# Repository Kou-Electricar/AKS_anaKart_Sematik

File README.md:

# AKS_anaKart_Sematik
araç kontrol kartı ana kartı

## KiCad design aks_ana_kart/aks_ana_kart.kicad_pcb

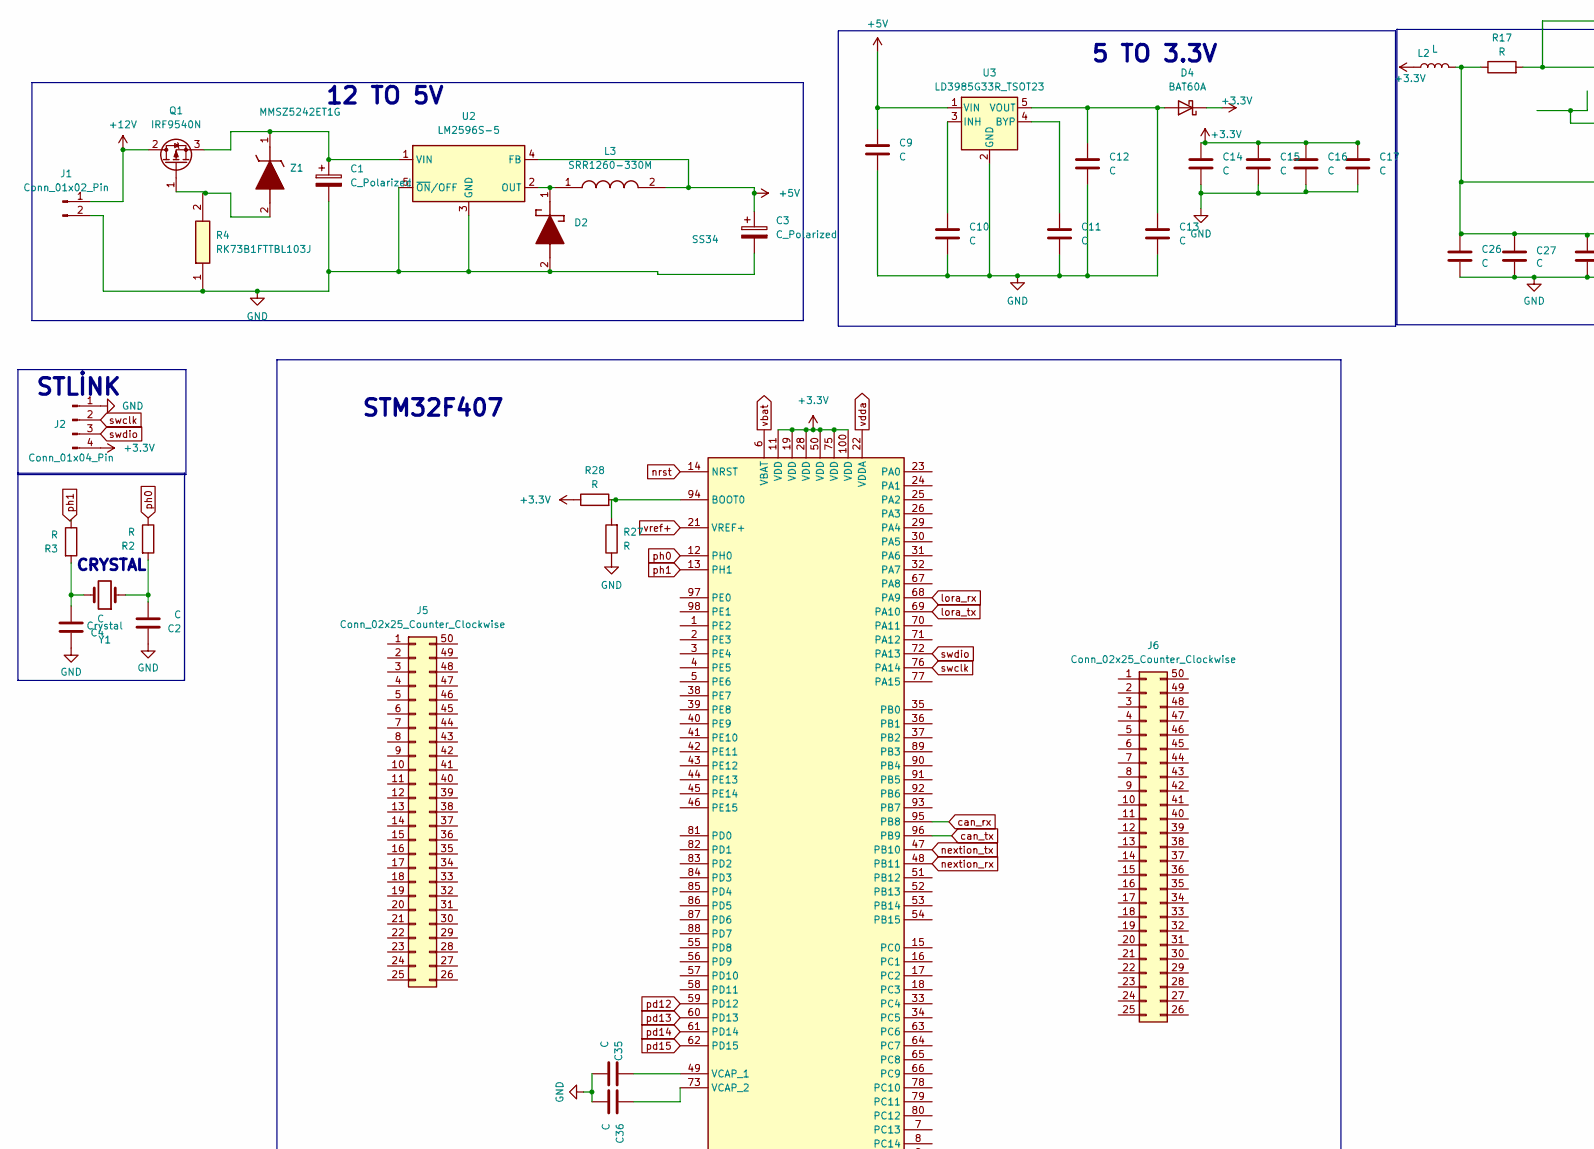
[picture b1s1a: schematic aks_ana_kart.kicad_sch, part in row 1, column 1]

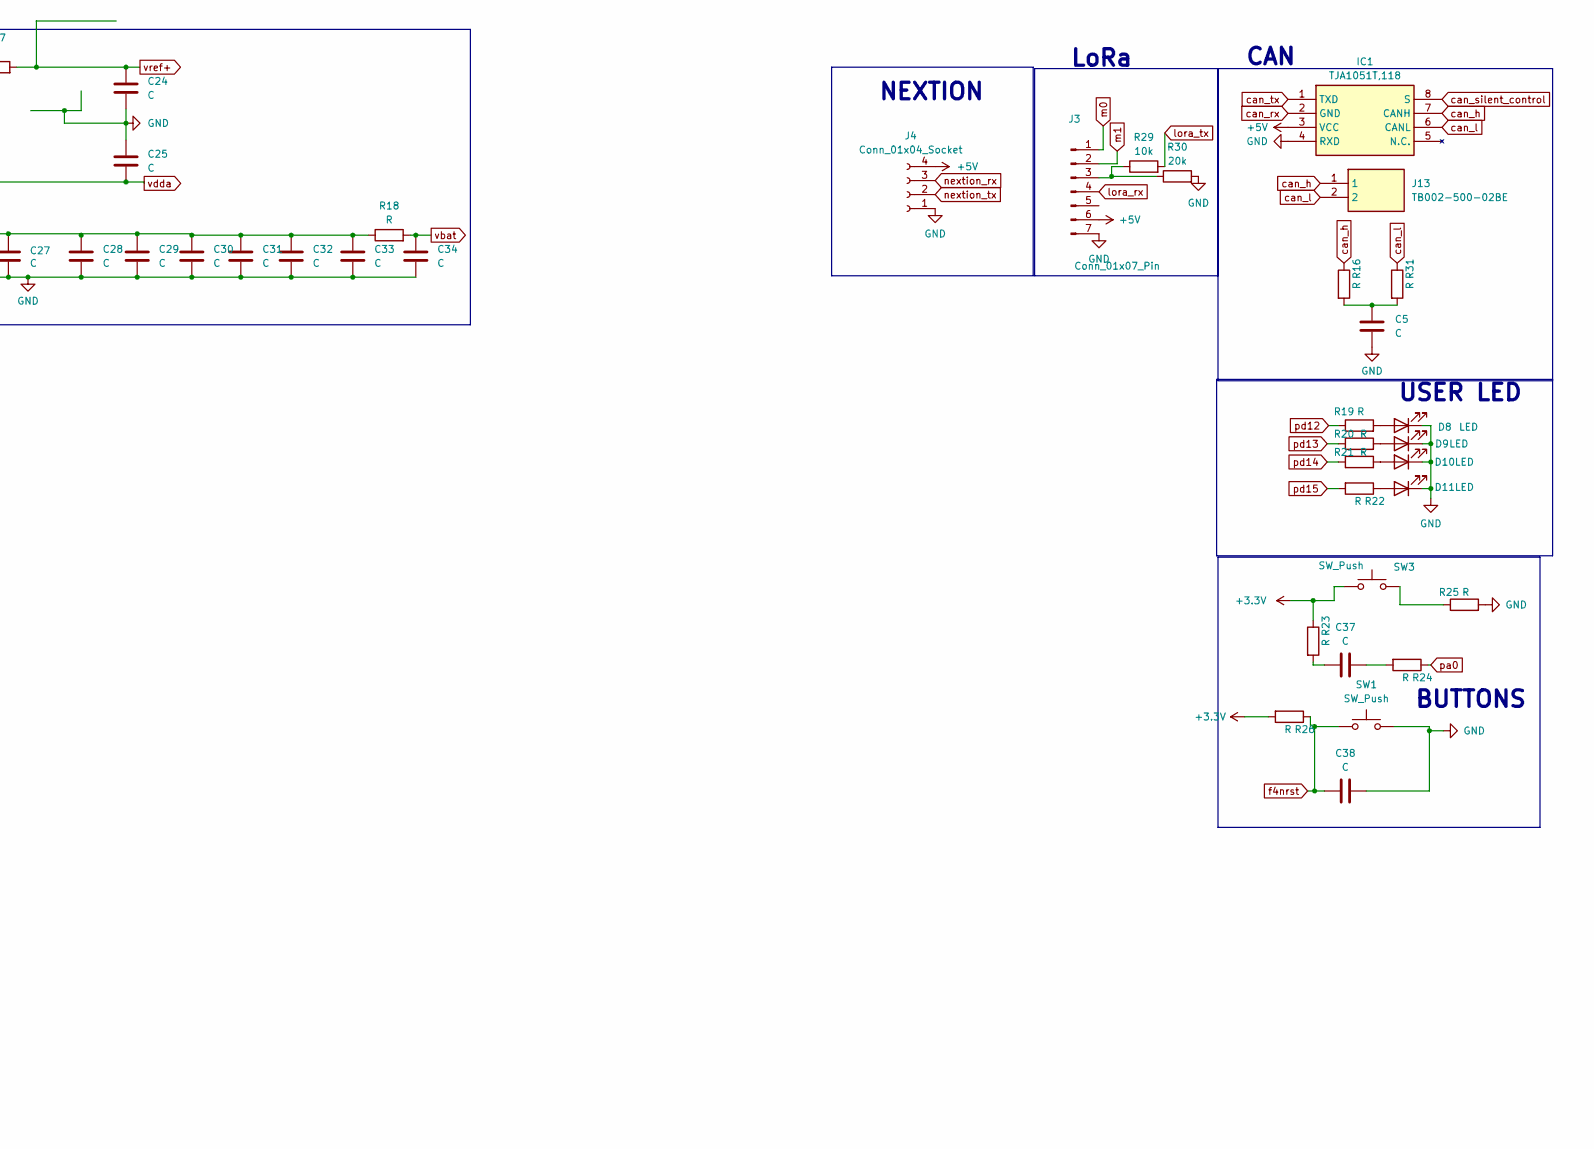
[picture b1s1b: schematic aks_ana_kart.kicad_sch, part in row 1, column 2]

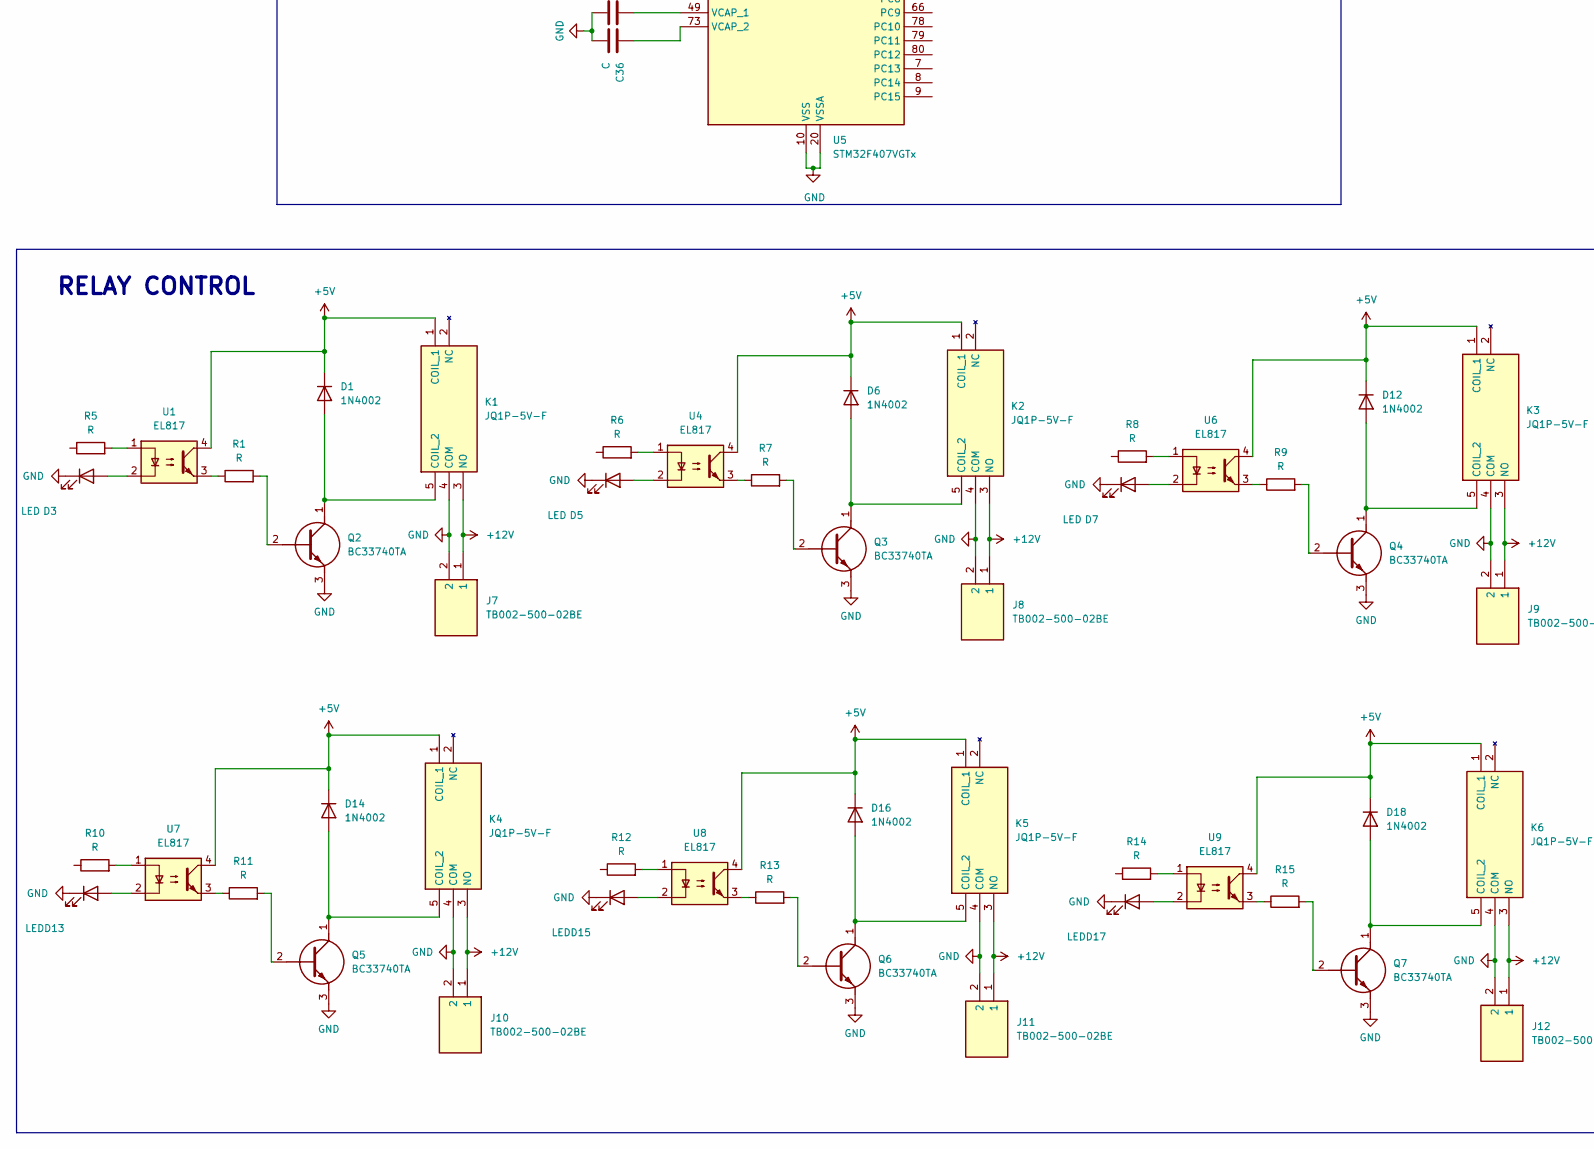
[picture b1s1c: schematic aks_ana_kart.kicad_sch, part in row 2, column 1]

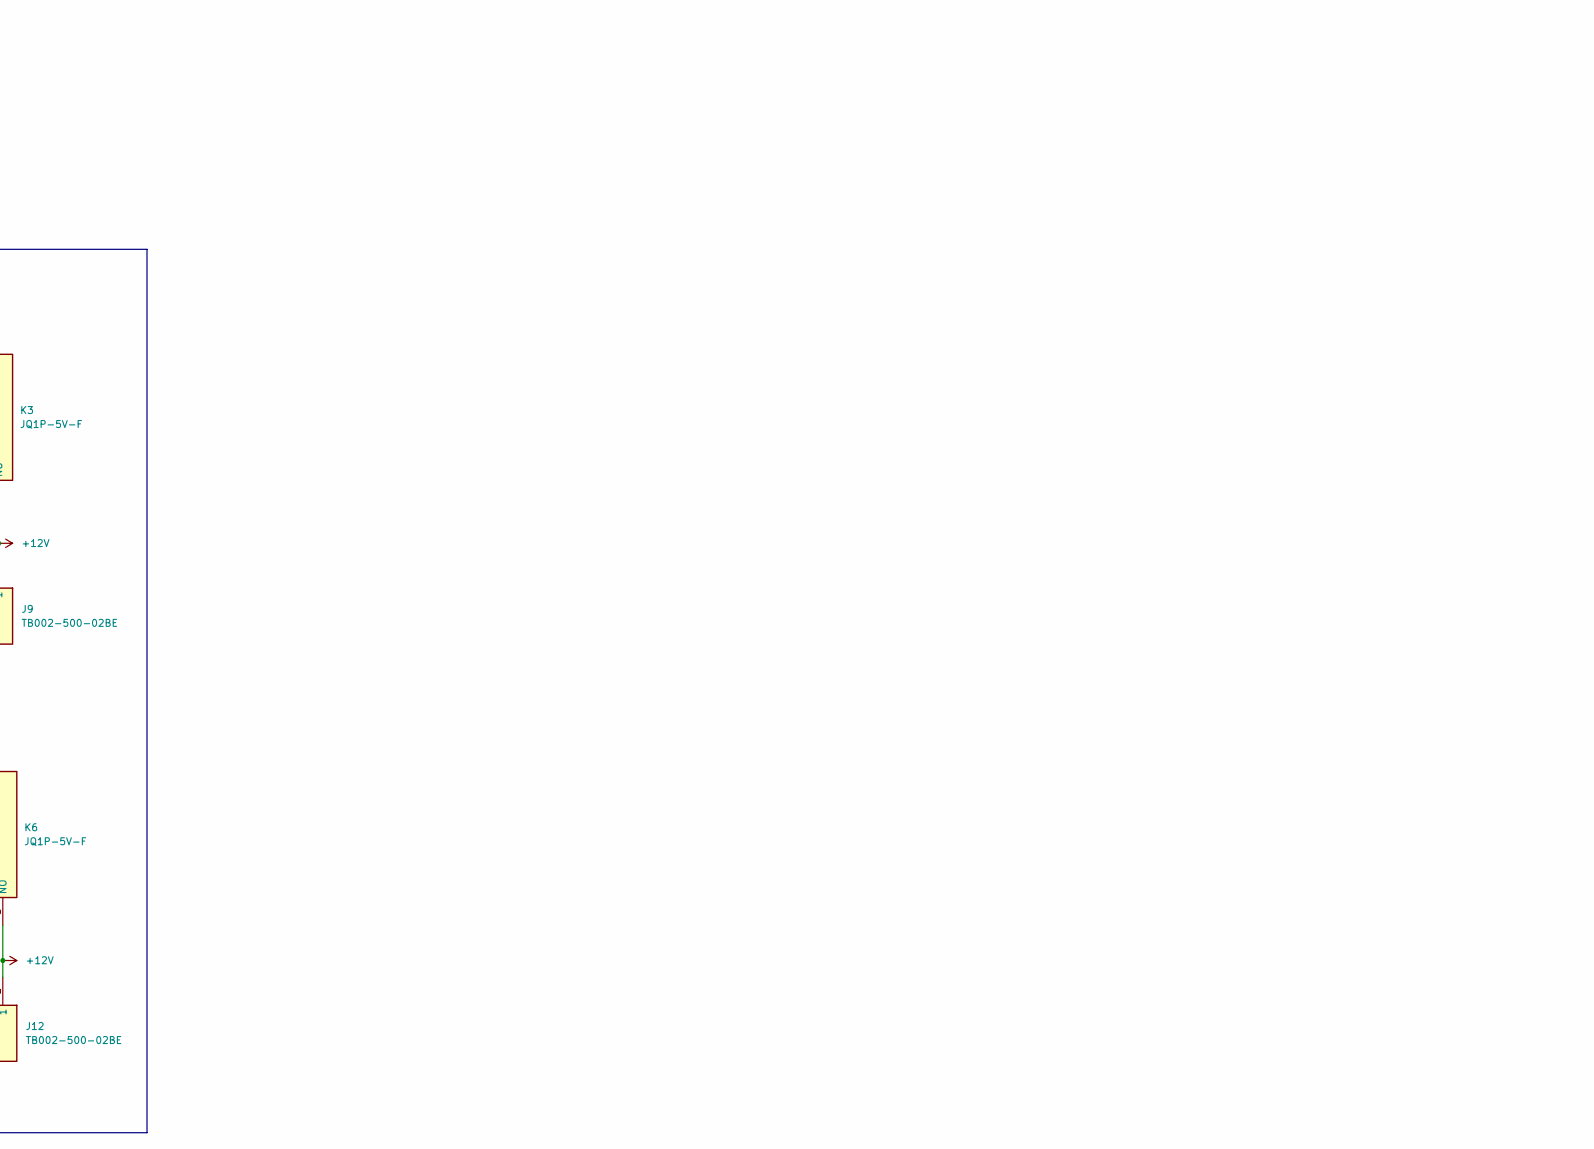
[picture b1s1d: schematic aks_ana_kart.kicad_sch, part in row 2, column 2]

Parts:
C1, C3: C_Polarized; CP_Radial_D6.3mm_P2.50mm
C2, C4, C5, C9, C10, C11, C12, C13, C14, C15, C16, C17, C24, C25, C26, C27, C28, C29, C30, C31, C32, C33, C34, C35, C36, C37, C38: C; C_0201_0603Metric
D1, D6, D12, D14, D16, D18: 1N4002; D_DO-41_SOD81_P7.62mm_Horizontal
D2: SS34; DIOM8059X256N; Mouser Part Number 512-SS34
D3, D5, D7, D8, D9, D10, D11, D13, D15, D17: LED; LED_0603_1608Metric
D4: BAT60A; D_SOD-323
IC1: TJA1051T,118; SOIC127P600X175-8N; Mouser Part Number 771-TJA1051T,118
J1: Conn_01x02_Pin; PinHeader_1x02_P1.27mm_Vertical
J2: Conn_01x04_Pin; PinHeader_1x04_P2.54mm_Vertical
J3: Conn_01x07_Pin; PinSocket_1x07_P1.00mm_Vertical
J4: Conn_01x04_Socket; JST_PH_B4B-PH-K_1x04_P2.00mm_Vertical
J5, J6: Conn_02x25_Counter_Clockwise; PinSocket_2x25_P2.54mm_Vertical
J7, J8, J9, J10, J11, J12, J13: TB002-500-02BE; TB00250002BE; Mouser Part Number 490-TB002-500-02BE
K1, K2, K3, K4, K5, K6: JQ1P-5V-F; JQ1P5VF; Mouser Part Number 769-JQ1P-5V-F
L2: L; L_0603_1608Metric
L3: SRR1260-330M; SRR1260-150M; Mouser Part Number 652-SRR1260-330M
Q1: IRF9540N; TO-220-3_Vertical
Q2, Q3, Q4, Q5, Q6, Q7: BC33740TA; Mouser Part Number 512-BC33740TA
R1, R2, R3, R5, R6, R7, R8, R9, R10, R11, R12, R13, R14, R15, R16, R17, R18, R19, R20, R21, R22, R23, R24, R25, R26, R27, R28, R31: R; R_0201_0603Metric
R4: RK73B1FTTBL103J; RESC0402X15N; Mouser Part Number 660-RK73B1FTTBL103J
R29: 10k; R_0201_0603Metric
R30: 20k; R_0201_0603Metric
SW1, SW3: SW_Push; SW_PUSH-12mm
U1, U4, U6, U7, U8, U9: EL817; DIP-4_W7.62mm
U2: LM2596S-5; TO-263-5_TabPin3
U3: LD3985G33R_TSOT23; TSOT-23-5
U5: STM32F407VGTx; LQFP-100_14x14mm_P0.5mm
Y1: Crystal; Crystal_HC52-8mm_Vertical
Z1: MMSZ5242ET1G; SOD3716X145N; Mouser Part Number 863-MMSZ5242ET1G

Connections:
+3.3V: C14.1, C15.1, C16.1, C17.1, D4.1 (K), J2.4, L2.1, R23.1, R26.2, R28.1, SW3.1, U5.11 (VDD), U5.19 (VDD), U5.28 (VDD), U5.50 (VDD), U5.75 (VDD), U5.100 (VDD)
+5V: C3.1, C9.1, D1.1 (K), D6.1 (K), D12.1 (K), D14.1 (K), D16.1 (K), D18.1 (K), IC1.3 (VCC), J3.6, J4.4, K1.1 (COIL_1), K2.1 (COIL_1), K3.1 (COIL_1), K4.1 (COIL_1), K5.1 (COIL_1), K6.1 (COIL_1), L3.2, U1.4, U2.4 (FB), U3.1 (VIN), U4.4, U6.4, U7.4, U8.4, U9.4
+12V: J1.1, J7.1, J8.1, J9.1, J10.1, J11.1, J12.1, K1.3 (NO), K2.3 (NO), K3.3 (NO), K4.3 (NO), K5.3 (NO), K6.3 (NO), Q1.2 (D)
GND: C1.2, C2.1, C3.2, C4.1, C5.1, C9.2, C10.2, C11.2, C12.2, C13.2, C14.2, C15.2, C16.2, C17.2, C24.2, C25.1, C26.2, C27.2, C28.2, C29.2, C30.2, C31.2, C32.2, C33.2, C34.2, C35.2, C36.2, C38.2, D2.2 (A), D3.1 (K), D5.1 (K), D7.1 (K), D8.1 (K), D9.1 (K), D10.1 (K), D11.1 (K), D13.1 (K), D15.1 (K), D17.1 (K), IC1.4 (RXD), J1.2, J2.1, J3.7, J4.1, J7.2, J8.2, J9.2, J10.2, J11.2, J12.2, K1.4 (COM), K2.4 (COM), K3.4 (COM), K4.4 (COM), K5.4 (COM), K6.4 (COM), Q2.3 (E), Q3.3 (E), Q4.3 (E), Q5.3 (E), Q6.3 (E), Q7.3 (E), R4.1, R25.2, R27.1, R30.2, SW1.2, U2.3 (GND), U2.5 (~ON/OFF), U3.2 (GND), U5.10 (VSS), U5.20 (VSSA), U5.27 (VSS), U5.74 (VSS), U5.99 (VSS); also elsewhere on the board
unnamed: C2.2, R2.2, Y1.1
unnamed: C4.2, R3.2, Y1.2
unnamed: C5.2, R16.2, R31.2
unnamed: C37.1, R23.2
unnamed: C37.2, R24.2
unnamed: D1.2 (A), K1.5 (COIL_2), Q2.1 (C)
unnamed: D2.1 (K), L3.1, U2.2 (OUT)
unnamed: D3.2 (A), U1.2
unnamed: C12.1, C13.1, D4.2 (A), U3.5 (VOUT)
unnamed: D5.2 (A), U4.2
unnamed: D6.2 (A), K2.5 (COIL_2), Q3.1 (C)
unnamed: D7.2 (A), U6.2
unnamed: D8.2 (A), R19.2
unnamed: D9.2 (A), R20.2
unnamed: D10.2 (A), R21.2
unnamed: D11.2 (A), R22.1
unnamed: D12.2 (A), K3.5 (COIL_2), Q4.1 (C)
unnamed: D13.2 (A), U7.2
unnamed: D14.2 (A), K4.5 (COIL_2), Q5.1 (C)
unnamed: D15.2 (A), U8.2
unnamed: D16.2 (A), K5.5 (COIL_2), Q6.1 (C)
unnamed: D17.2 (A), U9.2
unnamed: D18.2 (A), K6.5 (COIL_2), Q7.1 (C)
unnamed: J3.3, R29.1, R30.1
unnamed: Q1.1 (G), R4.2, Z1.2 (A)
unnamed: C1.1, Q1.3 (S), U2.1 (VIN), Z1.1 (K)
unnamed: Q2.2 (B), R1.2
unnamed: Q3.2 (B), R7.2
unnamed: Q4.2 (B), R9.2
unnamed: Q5.2 (B), R11.2
unnamed: Q6.2 (B), R13.2
unnamed: Q7.2 (B), R15.2
unnamed: R1.1, U1.3
unnamed: R5.2, U1.1
unnamed: R6.2, U4.1
unnamed: R7.1, U4.3
unnamed: R8.2, U6.1
unnamed: R9.1, U6.3
unnamed: R10.2, U7.1
unnamed: R11.1, U7.3
unnamed: R12.2, U8.1
unnamed: R13.1, U8.3
unnamed: R14.2, U9.1
unnamed: R15.1, U9.3
unnamed: R25.1, SW3.2
unnamed: C11.1, U3.4 (BYP)
unnamed: C10.1, U3.3 (INH)
unnamed: R27.2, R28.2, U5.94 (BOOT0)
unnamed: C35.1, U5.49 (VCAP_1)
unnamed: C36.1, U5.73 (VCAP_2)
can_h: IC1.7 (CANH), J13.1, R16.1
can_l: IC1.6 (CANL), J13.2, R31.1
can_rx: IC1.2 (GND), U5.95 (PB8)
can_silent_control: IC1.8 (S)
can_tx: IC1.1 (TXD), U5.96 (PB9)
f4nrst: C38.1, R26.1, SW1.1
lora_rx: J3.4, U5.68 (PA9)
lora_tx: R29.2, U5.69 (PA10)
m0: J3.1
m1: J3.2
nextion_rx: J4.3, U5.48 (PB11)
nextion_tx: J4.2, U5.47 (PB10)
nrst: U5.14 (NRST)
pa0: R24.1
pd12: R19.1, U5.59 (PD12)
pd13: R20.1, U5.60 (PD13)
pd14: R21.1, U5.61 (PD14)
pd15: R22.2, U5.62 (PD15)
ph0: R2.1, U5.12 (PH0)
ph1: R3.1, U5.13 (PH1)
swclk: J2.2, U5.76 (PA14)
swdio: J2.3, U5.72 (PA13)
vbat: C34.1, R18.2, U5.6 (VBAT)
vdda: C25.2, C26.1, C27.1, C28.1, C29.1, C30.1, C31.1, C32.1, C33.1, L2.2, R17.1, R18.1, U5.22 (VDDA); also elsewhere on the board
vref+: C24.1, R17.2, U5.21 (VREF+); also elsewhere on the board

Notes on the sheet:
CAN
LoRa
USER LED
STLİNK
5 TO 3.3V
CRYSTAL
NEXTION
RELAY CONTROL
12 TO 5V
BUTTONS
STM32F407

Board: 2 copper layers, 122 parts (9 on the bottom side), 74 nets, no tracks yet.

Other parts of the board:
C22, C23: C_Polarized; C_0603_1608Metric

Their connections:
GND: C22.2, C23.2; also elsewhere on the board
vdda: C23.1; also elsewhere on the board
vref+: C22.1; also elsewhere on the board

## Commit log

2024-10-13 Add files via upload
    6 röle ,tja1051 can,lora ,nextion,buck converter, stlink pinleri,geliştirme kartı pinleri
